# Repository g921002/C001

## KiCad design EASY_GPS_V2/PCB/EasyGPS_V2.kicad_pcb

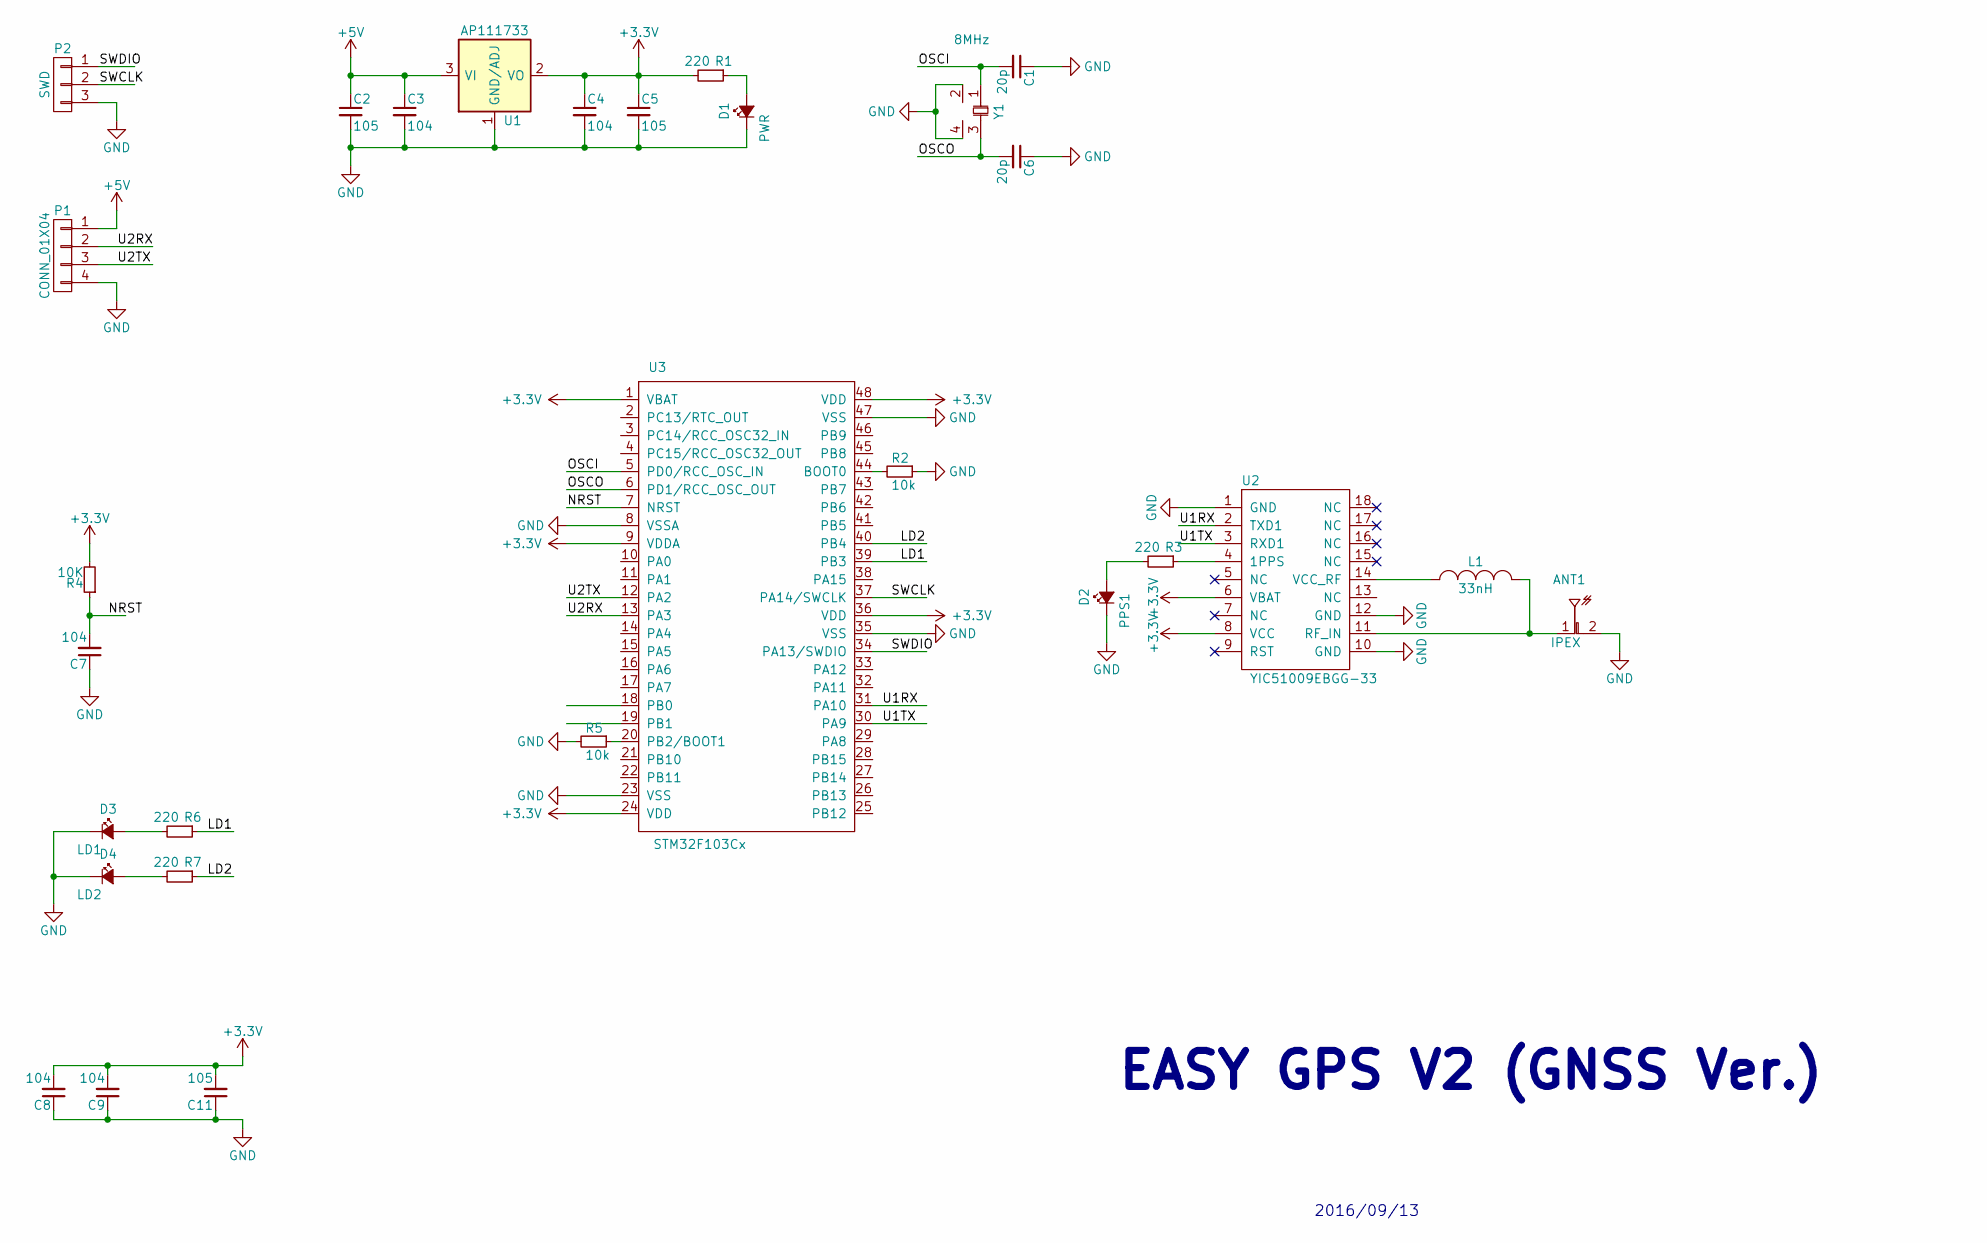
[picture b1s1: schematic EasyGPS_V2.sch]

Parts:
ANT1: IPEX; IPEX-Socket
C1, C6: 20p; C0805
C2, C5, C11: 105; C0805
C3, C4, C7, C8, C9: 104; C0805
D1: PWR; LED0805
D2: PPS1; LED0805
D3: LD1; LED0805
D4: LD2; LED0805
L1: 33nH; L0805
P1: CONN_01X04; PH-4P-2.0mm-D90
P2: SWD; PH-3P-2.0mm
R1, R3, R6, R7: 220; R0805
R2, R5: 10k; R0805
R4: 10K; R0805
U1: AP111733; SOT-223-4
U2: YIC51009EBGG-33
U3: STM32F103Cx; QFP48-7x7p0.5
Y1: 8MHz; Crystal-4-5032

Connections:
+3V3: C4.1, C5.1, C8.2, C9.2, C11.2, R1.2, R4.2, U1.2 (VO), U1.4 (VO), U2.6 (VBAT), U2.8 (VCC), U3.1 (VBAT), U3.9 (VDDA), U3.24 (VDD), U3.36 (VDD), U3.48 (VDD)
+5V: C2.1, C3.1, P1.1, U1.3 (VI)
/LD1: R6.1, U3.39 (PB3)
/LD2: R7.1, U3.40 (PB4)
/NRST: C7.2, R4.1, U3.7 (NRST)
/OSCI: C1.2, U3.5 (PD0/RCC_OSC_IN), Y1.1
/OSCO: C6.2, U3.6 (PD1/RCC_OSC_OUT), Y1.3
/SWCLK: P2.2, U3.37 (PA14/SWCLK)
/SWDIO: P2.1, U3.34 (PA13/SWDIO)
/U1RX: U2.2 (TXD1), U3.31 (PA10)
/U1TX: U2.3 (RXD1), U3.30 (PA9)
/U2RX: P1.2, U3.13 (PA3)
/U2TX: P1.3, U3.12 (PA2)
GND: ANT1.2, C1.1, C2.2, C3.2, C4.2, C5.2, C6.1, C7.1, C8.1, C9.1, C11.1, D1.1 (K), D2.1 (K), D3.1 (K), D4.1 (K), P1.4, P2.3, R2.1, R5.2, U1.1 (GND/ADJ), U2.1 (GND), U2.10 (GND), U2.12 (GND), U3.8 (VSSA), U3.23 (VSS), U3.35 (VSS), U3.47 (VSS), Y1.2, Y1.4; also elsewhere on the board
unnamed: ANT1.1, L1.2, U2.11 (RF_IN)
unnamed 15: D1.2 (A), R1.1; also elsewhere on the board
unnamed 16: D2.2 (A), R3.2; also elsewhere on the board
unnamed: D3.2 (A), R6.2
unnamed: D4.2 (A), R7.2
unnamed: L1.1, U2.14 (VCC_RF)
unnamed: R2.2, U3.44 (BOOT0)
unnamed: R3.1, U2.4 (1PPS)
unnamed: R5.1, U3.20 (PB2/BOOT1)

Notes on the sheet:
EASY GPS V2 (GNSS Ver.)
2016/09/13

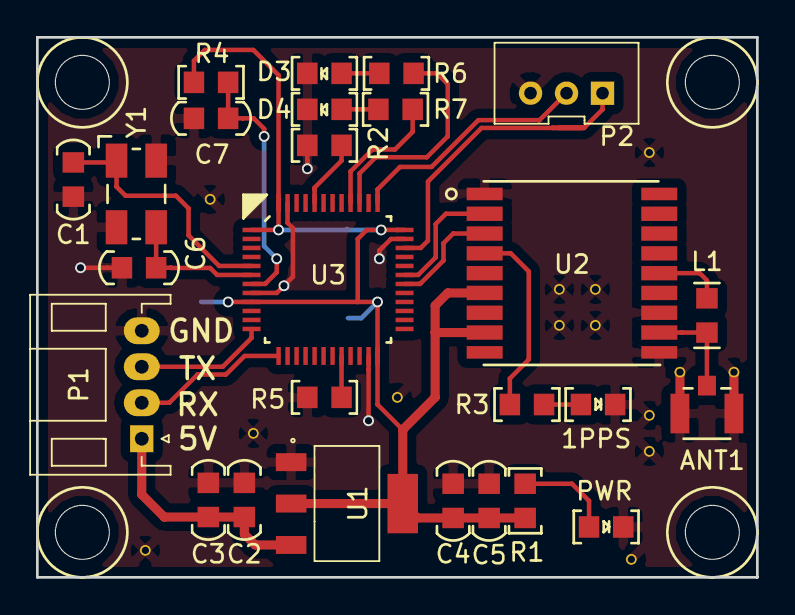
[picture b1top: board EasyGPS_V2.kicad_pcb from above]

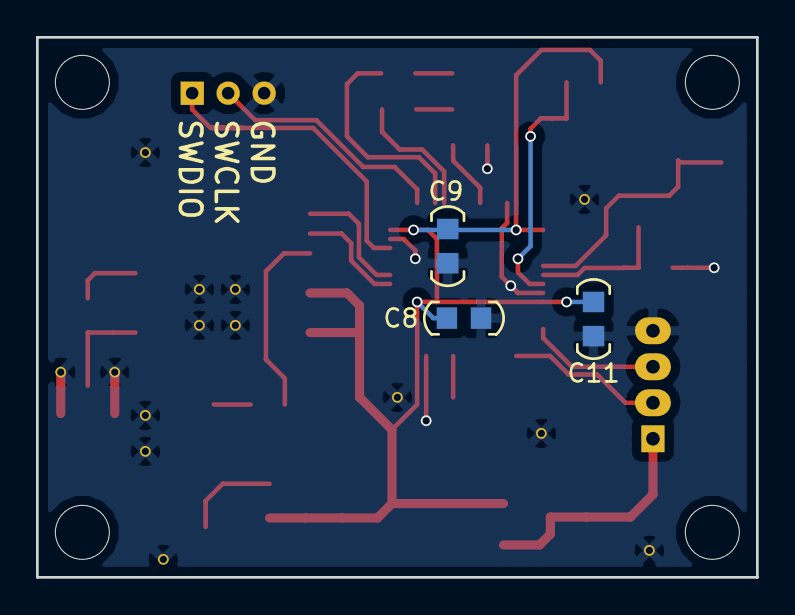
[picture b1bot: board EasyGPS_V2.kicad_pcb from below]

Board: 2 copper layers, 40.0 x 30.0 mm, 29 parts (3 on the bottom side), 23 nets.

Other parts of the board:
1PPS: PPS1; LED0805
PWR: PWR; LED0805

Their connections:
GND: 1PPS.1, PWR.1; also elsewhere on the board
unnamed 15: PWR.2; also elsewhere on the board
unnamed 16: 1PPS.2; also elsewhere on the board

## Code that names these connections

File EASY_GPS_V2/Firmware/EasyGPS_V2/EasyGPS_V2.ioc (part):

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Mcu.Name=STM32F103C(8-B)Tx
Mcu.Package=LQFP48
Mcu.UserName=STM32F103C8Tx
PA10.Mode=Asynchronous
PA10.Signal=USART1_RX
PA13.Mode=Serial_Wire
PA13.Signal=SYS_JTMS-SWDIO
PA14.Mode=Serial_Wire
PA14.Signal=SYS_JTCK-SWCLK
PA2.Mode=Asynchronous
PA2.Signal=USART2_TX
PA3.Mode=Asynchronous
PA3.Signal=USART2_RX
PA8.GPIOParameters=GPIO_Label
PA8.GPIO_Label=RSTG
PA8.Signal=GPIO_Output
PA9.Mode=Asynchronous
PA9.Signal=USART1_TX
PB3.GPIOParameters=GPIO_Label
PB3.GPIO_Label=LD1
PB3.Signal=GPIO_Output
PB4.GPIOParameters=GPIO_Label
PB4.GPIO_Label=LD2
PB4.Signal=GPIO_Output
PD0-OSC_IN.Mode=HSE-External-Oscillator
PD0-OSC_IN.Signal=RCC_OSC_IN
PD1-OSC_OUT.Mode=HSE-External-Oscillator
PD1-OSC_OUT.Signal=RCC_OSC_OUT
RCC.SYSCLKFreq_VALUE=72000000
RCC.SYSCLKSource=RCC_SYSCLKSOURCE_PLLCLK
board=EasyGPS_V2

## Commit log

2017-06-11 第一次測試
2017-06-11 刪除測試
2017-06-11 EasyGPS GNSS Module New
